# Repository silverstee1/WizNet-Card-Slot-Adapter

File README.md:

# WizNet-Card-Slot-Adapter
WizNet Card Slot Adapter for the Nintendo Gamecube Front Memory card slots based on the ETH2GC project by webhdx + Extrems utilizing either the W5500/W6100 mini modules found on Aliexpress, etc.

Must be used with Swiss-gc

Use Swiss build 1788 or the latest ~~artifact build 1744+~~  it has the new hypervisor driver for W6100 and W5500 allowing you to use it for Mario Kart LAN etc.

**Assembly Video**

https://youtu.be/p_-DQ5K5pyQ

**Aliexpress Links**

W6100 Mini Module
https://www.aliexpress.us/item/3256805107146668.html

W5500 Mini Module
https://www.aliexpress.us/item/3256804674673261.html

Snips used for trimming pieces of pcb/pin headers.
https://www.aliexpress.us/item/2251832627908078.html

Screws 2x5MM

https://www.aliexpress.us/item/3256802919903942.html

https://www.aliexpress.us/item/3256806490428816.html

Build Details
=====================================
The PCB must be ordered (e.g. from jlcpcb) in 1.6mm thickness with surface finish ENIG at minimum.

You'll want to lay the Card slot adapter pcb center over top of the module making the module and pcb as flush together as possible and solder pin by pin the module to the pcb.

**3D Printed Case Enclosure**

You'll need to 3D print the case enclosure Top and Bottom pieces from the Case folder to use it in your Memcard Slot preferably on an FDM printer, 
the case screws are countersunk self tapping M2x5 screws.

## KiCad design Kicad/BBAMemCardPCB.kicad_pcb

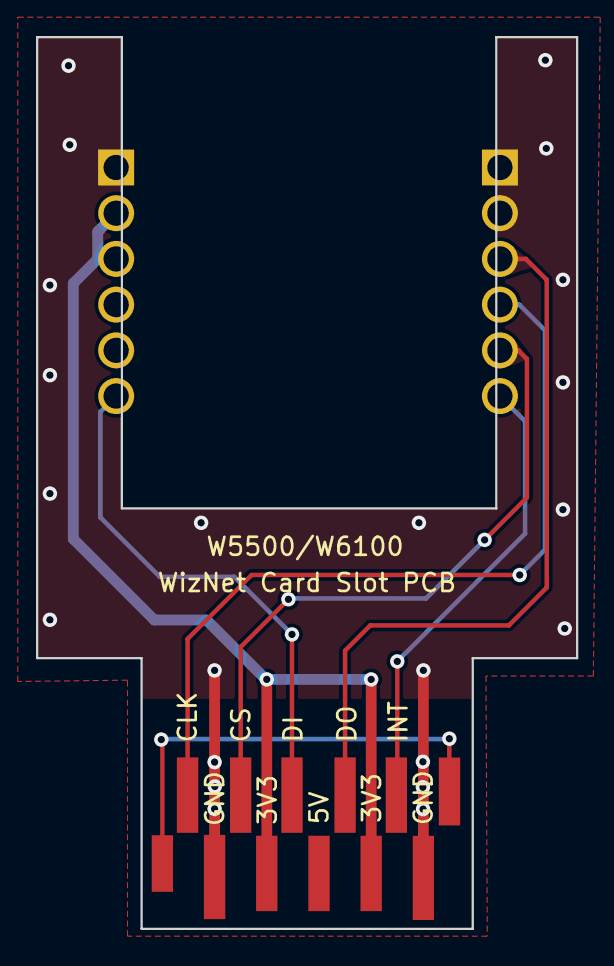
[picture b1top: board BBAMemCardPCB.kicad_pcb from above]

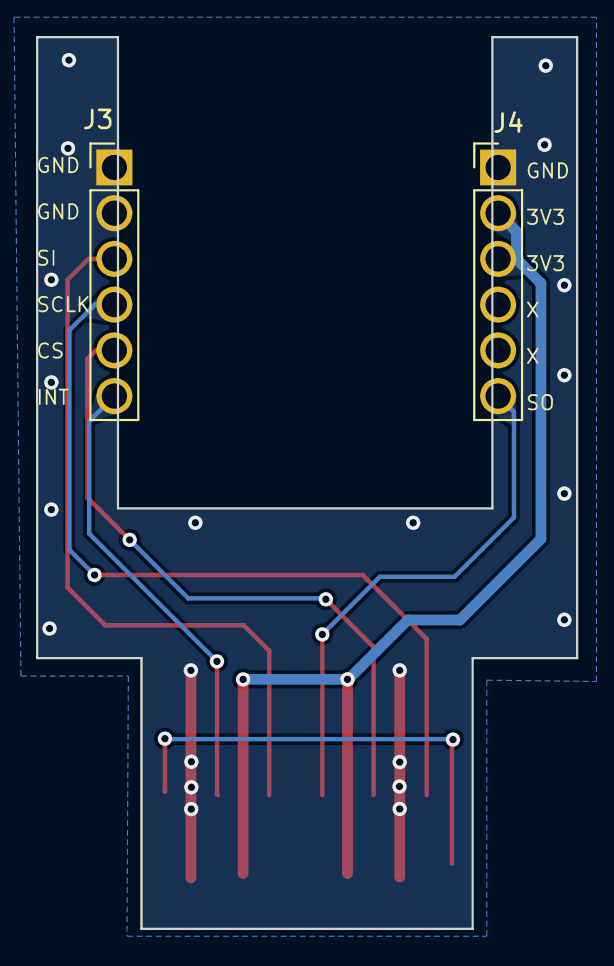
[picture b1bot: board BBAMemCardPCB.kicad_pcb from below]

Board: 2 copper layers, 30.0 x 49.5 mm, 3 parts (2 on the bottom side), 8 nets.

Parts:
J1: GC_MEMCARD
J3, J4: Conn_01x06; PinHeader_1x06_P2.54mm_Vertical

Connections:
/CS: J1.9 (CS), J3.5
/GND: J1.2 (GND@2), J1.10 (GND@10), J3.1, J3.2, J4.1
/INT: J1.3 (INT), J3.6
/SCK: J1.11 (CLK), J3.4
/SI: J1.5 (DO), J3.3
/SO: J1.7 (DI), J4.6
/VCC: J1.4 (3V3@4), J1.8 (3V3@8), J4.2, J4.3
unnamed: J1.1 (EXTIN), J1.12 (EXTOUT)

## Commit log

2024-11-04 added project files
    uploaded project
2025-03-03 Update README.md
    updated screw link
